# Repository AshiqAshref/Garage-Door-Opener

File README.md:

# Smart Garage Door Opener

A complete IoT garage door opener system featuring secure Bluetooth Low Energy (BLE) communication, ESP32-C3 microcontroller, custom PCB design, and Android mobile application.

## 🚀 Project Overview

This project implements a modern, secure garage door opener that can be controlled via a smartphone app. The system features:

- **Secure BLE Communication**: Encrypted pairing and authentication
- **ESP32-C3 Based Controller**: Low-power WiFi/BLE microcontroller
- **Custom PCB Design**: Professional circuit board with integrated power management
- **Android Mobile App**: Modern Material Design 3 interface
- **Visual Feedback**: 8-digit LED matrix display for status and pairing codes
- **Physical Controls**: Manual pairing button and factory reset capability

## 📁 Project Structure

```
Garage Door Opener Root/
├── Garage Door Opener Circuit/        # KiCad PCB design files
│   ├── GarageOpener.kicad_sch         # Main schematic
│   ├── GarageOpener.kicad_pcb         # PCB layout
│   ├── production files/              # Gerber files for manufacturing
│   └── parts.txt                      # Bill of materials
├── Garage Door Opener Code/
│   ├── ESP32/                         # Firmware for ESP32-C3
│   │   └── Garage Door Opener/
│   │       ├── src/main.cpp           # Main firmware code
│   │       └── platformio.ini        # PlatformIO configuration
│   └── Android/                       # Android mobile application
│       └── GarageOpenerUI/
│           └── app/src/main/          # Android app source code
├── LICENSE                            # Project license
└── README.md                          # This file
```

## 🔧 Hardware Components

### Main Components
- **ESP32-C3-MINI-1U-N4**: Main microcontroller with WiFi/BLE
- **5V Relay Module**: Controls garage door motor
- **MAX7219 LED Matrix**: 8-digit display for status and pairing codes
- **Buck Converter**: Efficient 5V power supply from mains voltage
- **3.3V Regulator**: Powers ESP32 and logic circuits

### Key Features
- **Input Voltage**: 3.8V - 32V DC input range
- **Power Consumption**: Low-power design with sleep modes
- **Protection**: ESD protection, overcurrent protection
- **Connectivity**: Micro USB for user cusom programming and debugging
- **User Interface**: Physical pairing button, LED status indicators

### PCB Specifications
- **Board Size**: Compact form factor for enclosure mounting
- **Layers**: Multi-layer design for proper power distribution
- **Components**: Surface mount components for reliability
- **Connectors**: Screw terminals for garage door connections

## 💻 Software Features

### ESP32 Firmware
- **Secure BLE Server**: Implements encrypted communication
- **Pairing Management**: Secure device pairing with passkey display
- **Display Controller**: Real-time status updates on LED matrix
- **Memory Management**: Persistent storage of paired devices
- **Factory Reset**: Complete system reset capability

### Android Application
- **Modern UI**: Material Design 3 with Jetpack Compose
- **Device Discovery**: Automatic BLE device scanning
- **Secure Pairing**: Handles BLE security and authentication
- **Device Management**: Save and manage multiple garage door openers
- **Real-time Status**: Live connection status and feedback

## 🔐 Security Features

- **Encrypted BLE Communication**: All data transmitted over encrypted channels
- **Device Authentication**: Secure pairing with passkey verification
- **Bonded Devices**: Only previously paired devices can connect
- **Timeout Protection**: Pairing mode automatically times out
- **Factory Reset**: Complete security reset capability

## 🛠️ Installation & Setup

### Hardware Assembly

1. **PCB Assembly**: Solder all components according to the schematic
2. **Power Connection**: Connect 5-32V DC power supply to input terminals
3. **Relay Wiring**: Connect relay outputs to garage door motor controls
4. **Display Connection**: Wire MAX7219 LED matrix to designated pins
5. **Enclosure**: Mount PCB in weatherproof enclosure

### Firmware Installation

1. **Install PlatformIO**: Set up PlatformIO IDE or VS Code extension
2. **Clone Repository**: Download project files
3. **Configure Platform**: Verify ESP32-C3 platform configuration
4. **Build & Upload**: Compile and flash firmware to ESP32

```bash
cd "Garage Door Opener Code/ESP32/Garage Door Opener"
pio run --target upload
```

### Android App Installation
1. **Easy Install** : Pre built app can be found in ```Garage Door Opener Code/Android/GarageOpenerUI/app/release/app-release.apk``` 

### Android App build
1. **Android Studio**: Open project in Android Studio
2. **Dependencies**: Sync Gradle dependencies
3. **Build Configuration**: Configure signing and build settings
4. **Install**: Build and install APK on Android device

```bash
cd "Garage Door Opener Code/Android/GarageOpenerUI"
./gradlew assembleRelease
```

## 📱 Usage Instructions

### Initial Setup

1. **Power On**: Connect power to the garage door opener
2. **Pairing Mode**: Press and hold the pairing button for 5 seconds
3. **Mobile App**: Open the Android app and scan for devices
4. **Select Device**: Choose "Garage" from the discovered devices list
5. **Enter Passkey**: Input the 6-digit code displayed on the LED matrix
6. **Complete Pairing**: Confirm pairing on both devices

### Daily Operation

1. **Open App**: Launch the Garage Opener app on your phone
2. **Connect**: App automatically connects to paired device
3. **Control**: Tap the garage door button to operate
4. **Status**: Monitor connection status via app interface

### Advanced Features

- **Multiple Devices**: Pair multiple garage door openers
- **Device Management**: Remove or re-pair devices as needed
- **Factory Reset**: Hold pairing button for 10 seconds to reset

## 🔌 Pin Configuration

### ESP32-C3 Pin Assignments
```cpp
#define RELAY_PIN 12        // Garage door relay control
#define BUTTON_PIN 13       // Pairing/reset button
#define DIN_PIN 21          // MAX7219 data input
#define CS_PIN 19           // MAX7219 chip select
#define CLK_PIN 18          // MAX7219 clock
```

### Power Requirements
- **Input Voltage**: 5V - 32V DC
- **ESP32 Current**: ~80mA active, ~10µA deep sleep
- **Relay Current**: ~70mA when activated
- **Display Current**: ~20mA typical

## 🐛 Troubleshooting

### Common Issues

**Cannot pair device:**
- Ensure Bluetooth is enabled on phone
- Verify device is in pairing mode (LED shows passkey)
- Check app permissions for Bluetooth access

**Relay not activating:**
- Verify power supply voltage (5V minimum)
- Check relay connections and wiring
- Test relay manually with multimeter

**Display not working:**
- Confirm MAX7219 connections and power
- Verify pin assignments in firmware
- Check display module with simple test code

**Connection drops frequently:**
- Reduce distance between phone and device
- Check for interference from other 2.4GHz devices
- Verify phone's Bluetooth Low Energy support

## 🔧 Development

### Building from Source

**Requirements:**
- PlatformIO Core 6.0+
- Android Studio Arctic Fox+
- ESP32 Arduino Core 2.0+
- Android API Level 30+

**ESP32 Development:**
```bash
# Install dependencies
pio pkg install

# Build firmware
pio run

# Upload to device
pio run --target upload

# Monitor serial output
pio device monitor
```

**Android Development:**
```bash
# Build debug APK
./gradlew assembleDebug

# Run tests
./gradlew test

# Generate release APK
./gradlew assembleRelease
```

### Code Structure

**ESP32 Firmware:**
- `main.cpp`: Main application logic and BLE server
- `LedController.hpp`: MAX7219 display management
- `platformio.ini`: Build configuration and dependencies

**Android Application:**
- `MainActivity.kt`: Main UI and app lifecycle
- `BleService.kt`: Bluetooth Low Energy communication
- `build.gradle.kts`: Build configuration and dependencies

## 📋 Bill of Materials (BOM)

### Critical Components
| Component | Part Number | Quantity | Description |
|-----------|-------------|----------|-------------|
| ESP32-C3-MINI-1U-N4 | ESP32-C3-MINI-1U-N4 | 1 | Main microcontroller |
| Relay | SRD-05VDC-SL-C | 1 | 5V SPDT relay |
| Buck Converter IC | TBD | 1 | 5V switching regulator |
| LED Matrix | MAX7219 8-digit | 1 | Status display |
| Capacitors | Various | Multiple | Power filtering |
| Resistors | Various | Multiple | Pull-ups and current limiting |

*See `parts.txt` for complete component specifications*

## 🤝 Contributing

Contributions are welcome! Please follow these guidelines:

1. **Fork the Repository**: Create your own fork
2. **Create Feature Branch**: `git checkout -b feature/new-feature`
3. **Commit Changes**: Use descriptive commit messages
4. **Push Branch**: `git push origin feature/new-feature`
5. **Create Pull Request**: Submit PR with detailed description

### Development Standards
- Follow existing code style and formatting
- Add comments for complex logic
- Test thoroughly before submitting
- Update documentation as needed

## 📄 License

This project is licensed under the MIT License - see the [LICENSE](LICENSE) file for details.

## ⚠️ Safety Warning

**ELECTRICAL SAFETY**: This device interfaces with garage door motors that operate at dangerous voltages. Installation should only be performed by qualified electricians. Always disconnect power before making connections.

**SECURITY**: While this system implements encryption, no system is 100% secure. Use appropriate physical security measures for your garage.

## 📞 Support

For questions, issues, or contributions:
- **Issues**: Use GitHub Issues for bug reports
- **Discussions**: GitHub Discussions for general questions
- **Email**: Contact project maintainer for urgent issues

## 🔄 Version History

- **v1.0**: Initial release with basic BLE functionality
- **Future**: Planned features include WiFi connectivity, web interface, and voice control integration

---

**Built with ❤️ for the maker community**

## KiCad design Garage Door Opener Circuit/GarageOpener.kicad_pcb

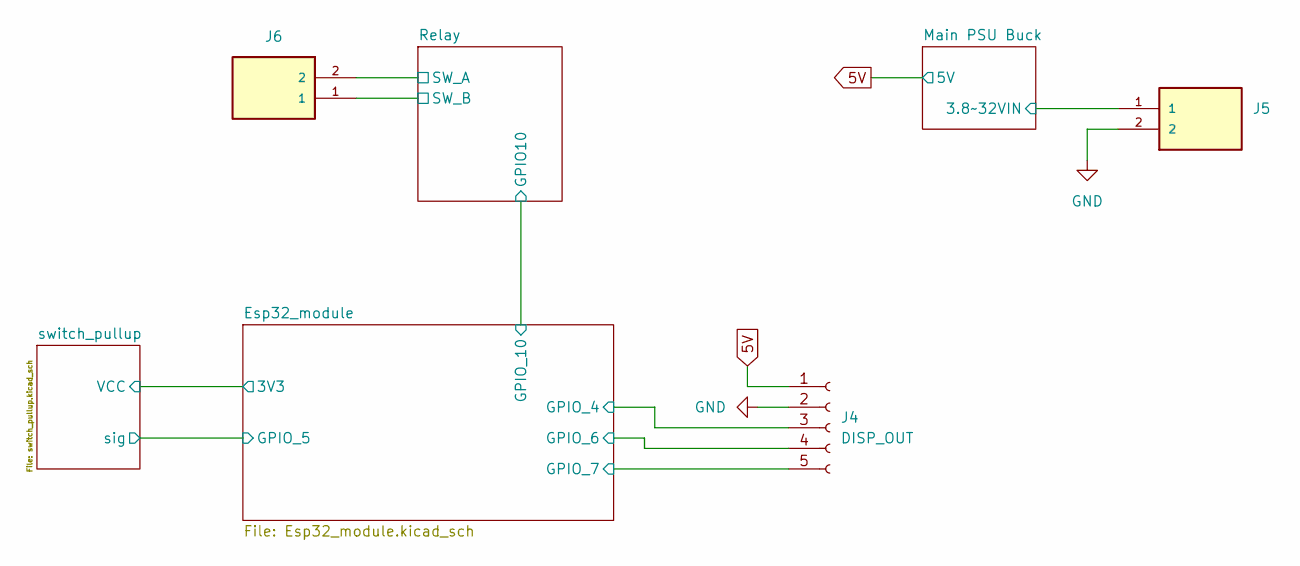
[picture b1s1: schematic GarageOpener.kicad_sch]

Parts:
J4: DISP_OUT; PinHeader_1x05_P2.54mm_Vertical
J5, J6: TB002-500-02BE; CUI_TB002-500-02BE

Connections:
5V: J4.1; also elsewhere on the board
/Esp32_module/GPIO_4: J4.3; also elsewhere on the board
/Esp32_module/GPIO_6: J4.4; also elsewhere on the board
/Esp32_module/GPIO_7: J4.5; also elsewhere on the board
/Main PSU Buck/3.8~32VIN: J5.1; also elsewhere on the board
/Relay/SW_A: J6.2; also elsewhere on the board
/Relay/SW_B: J6.1; also elsewhere on the board
GND: J4.2, J5.2; also elsewhere on the board

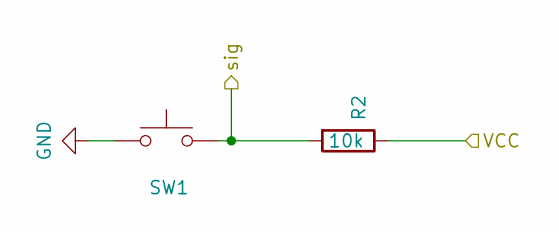
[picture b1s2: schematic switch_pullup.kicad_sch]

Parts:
R2: 10k; R_0402_1005Metric
SW1: SW_Push; SW_SPST_PTS645Sx43SMTR92

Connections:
3V3: R2.1; also elsewhere on the board
/Esp32_module/GPIO_5: R2.2, SW1.2; also elsewhere on the board
GND: SW1.1; also elsewhere on the board

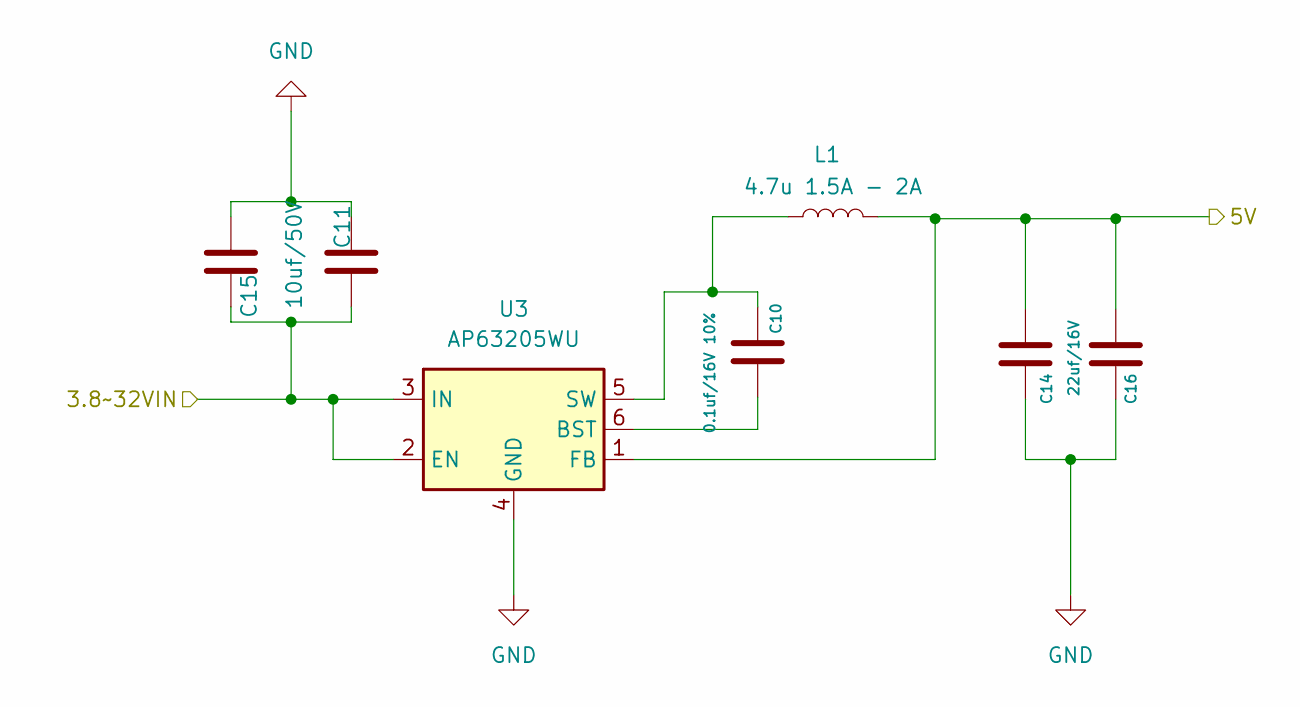
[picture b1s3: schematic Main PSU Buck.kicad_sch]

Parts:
C10: 0.1uf/16V 10%; C_0201_0603Metric
C11, C15: 10uf/50V; CAPC3225X270N
C14, C16: 22uf/16V; CAPC1608X100N
L1: 4.7u 1.5A - 2A; IND_NRS5030T100MMGJ_TAY
U3: AP63205WU; TSOT-23-6

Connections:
5V: C14.1, C16.1, L1.2, U3.1 (FB); also elsewhere on the board
/Main PSU Buck/3.8~32VIN: C11.2, C15.2, U3.2 (EN), U3.3 (IN); also elsewhere on the board
GND: C11.1, C14.2, C15.1, C16.2, U3.4 (GND); also elsewhere on the board
unnamed: C10.2, U3.6 (BST)
unnamed: C10.1, L1.1, U3.5 (SW)

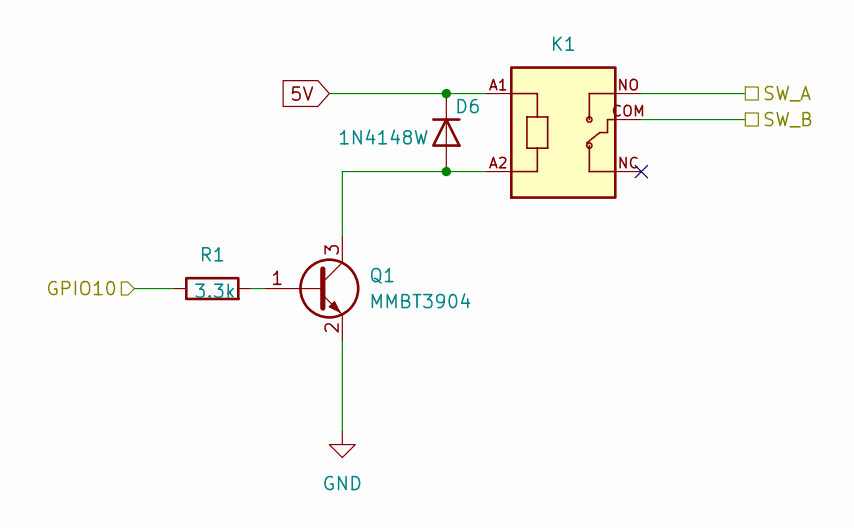
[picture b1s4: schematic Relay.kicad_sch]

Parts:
D6: 1N4148W; D_SOD-123
K1: SRD-05VDC-SL-C; RELAY_SRD-05VDC-SL-C
Q1: MMBT3904; SOT-23
R1: 3.3k; R_0603_1608Metric

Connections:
5V: D6.1 (K), K1.A1; also elsewhere on the board
/Esp32_module/GPIO_10: R1.1; also elsewhere on the board
/Relay/SW_A: K1.NO; also elsewhere on the board
/Relay/SW_B: K1.COM; also elsewhere on the board
GND: Q1.2 (E); also elsewhere on the board
unnamed: D6.2 (A), K1.A2, Q1.3 (C)
unnamed: Q1.1 (B), R1.2

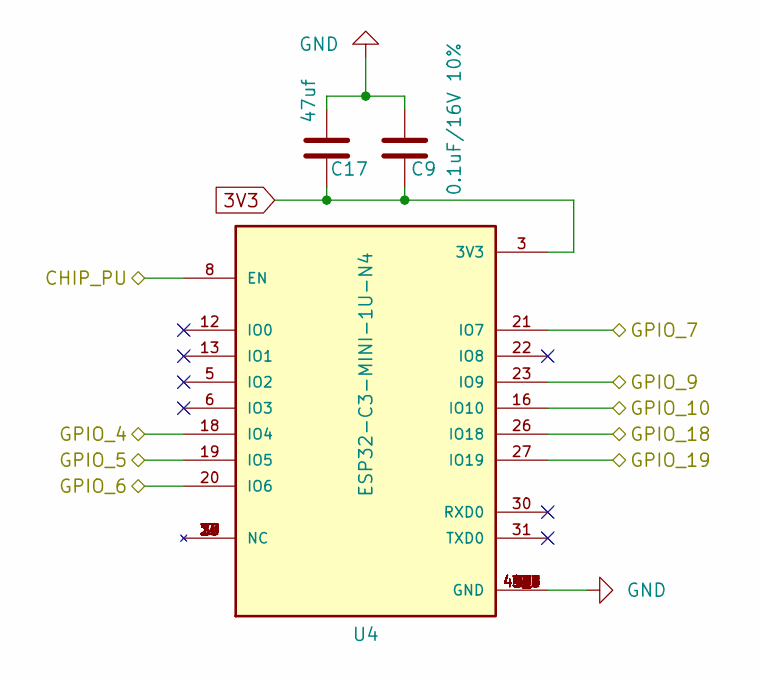
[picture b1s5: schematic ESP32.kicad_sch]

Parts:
C9: 0.1uF/16V 10%; VARC3216X85N
C17: 47uf; C_1206_3216Metric
U4: ESP32-C3-MINI-1U-N4; XCVR_ESP32-C3-MINI-1U-N4; PARTREV v1.0

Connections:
3V3: C9.1, C17.1, U4.3 (3V3); also elsewhere on the board
/Esp32_module/ESP32/CHIP_PU: U4.8 (EN); also elsewhere on the board
/Esp32_module/ESP32/GPIO_9: U4.23 (IO9); also elsewhere on the board
/Esp32_module/ESP32/GPIO_18: U4.26 (IO18); also elsewhere on the board
/Esp32_module/ESP32/GPIO_19: U4.27 (IO19); also elsewhere on the board
/Esp32_module/GPIO_4: U4.18 (IO4); also elsewhere on the board
/Esp32_module/GPIO_5: U4.19 (IO5); also elsewhere on the board
/Esp32_module/GPIO_6: U4.20 (IO6); also elsewhere on the board
/Esp32_module/GPIO_7: U4.21 (IO7); also elsewhere on the board
/Esp32_module/GPIO_10: U4.16 (IO10); also elsewhere on the board
GND: C9.2, C17.2, U4.1 (GND), U4.2 (GND), U4.11 (GND), U4.14 (GND), U4.36 (GND), U4.37 (GND), U4.38 (GND), U4.39 (GND), U4.40 (GND), U4.41 (GND), U4.42 (GND), U4.43 (GND), U4.44 (GND), U4.45 (GND), U4.46 (GND), U4.47 (GND), U4.48 (GND), U4.49_1 (GND), U4.49_2 (GND), U4.49_3 (GND), U4.49_4 (GND), U4.49_5 (GND), U4.49_6 (GND), U4.49_7 (GND), U4.49_8 (GND), U4.49_9 (GND), U4.50 (GND), U4.51 (GND), U4.52 (GND), U4.53 (GND); also elsewhere on the board

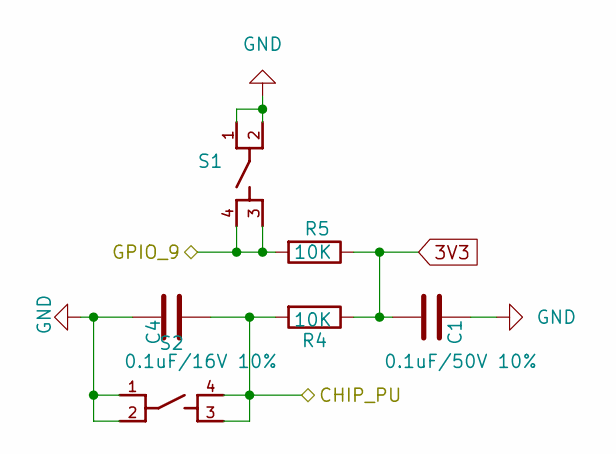
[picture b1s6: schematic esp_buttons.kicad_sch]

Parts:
C1: 0.1uF/50V 10%; C_0201_0603Metric
C4: 0.1uF/16V 10%; C_0201_0603Metric
R4, R5: 10K; R_0402_1005Metric
S1, S2: PTS526_SMG15_SMTR2_LFS; SW_PTS526_SMG15_SMTR2_LFS

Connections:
3V3: C1.1, R4.1, R5.1; also elsewhere on the board
/Esp32_module/ESP32/CHIP_PU: C4.2, R4.2, S2.3, S2.4; also elsewhere on the board
/Esp32_module/ESP32/GPIO_9: R5.2, S1.3, S1.4; also elsewhere on the board
GND: C1.2, C4.1, S1.1, S1.2, S2.1, S2.2; also elsewhere on the board

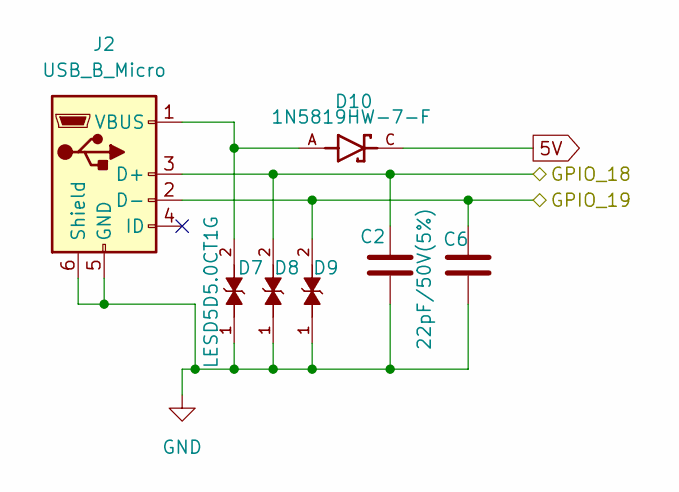
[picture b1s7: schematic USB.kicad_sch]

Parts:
C2, C6: 22pF/50V(5%); C_0201_0603Metric
D7, D8, D9: LESD5D5.0CT1G; TVS_LESD5D5.0CT1G; PARTREV O
D10: 1N5819HW-7-F; SOD3715X145N; PARTREV 18-2; DigiKey_Part_Number 1N5819HW-FDITR-ND
J2: USB_B_Micro; USB_Micro-B_Amphenol_10118194_Horizontal

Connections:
5V: D10.C; also elsewhere on the board
/Esp32_module/ESP32/GPIO_18: C2.1, D8.2, J2.3 (D+); also elsewhere on the board
/Esp32_module/ESP32/GPIO_19: C6.1, D9.2, J2.2 (D-); also elsewhere on the board
GND: C2.2, C6.2, D7.1, D8.1, D9.1, J2.5 (GND), J2.6 (Shield); also elsewhere on the board
unnamed: D7.2, D10.A, J2.1 (VBUS)

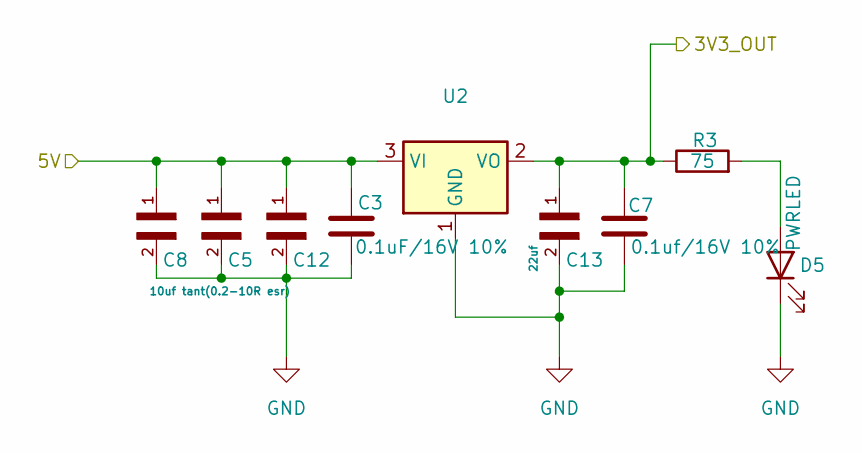
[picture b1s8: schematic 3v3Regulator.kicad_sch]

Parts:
C3: 0.1uF/16V 10%; VARC3216X85N
C5, C8, C12: 10uf tant(0.2-10R esr); C_1206_3216Metric
C7: 0.1uf/16V 10%; VARC3216X85N
C13: 22uf; C_1206_3216Metric
D5: PWRLED; 0603
R3: 75; R_0402_1005Metric
U2: AMS1117-3.3; SOT-223-3_TabPin2

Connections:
3V3: C7.1, C13.1, R3.1, U2.2 (VO); also elsewhere on the board
5V: C3.1, C5.1, C8.1, C12.1, U2.3 (VI); also elsewhere on the board
GND: C3.2, C5.2, C7.2, C8.2, C12.2, C13.2, D5.1 (K), U2.1 (GND); also elsewhere on the board
unnamed: D5.2 (A), R3.2

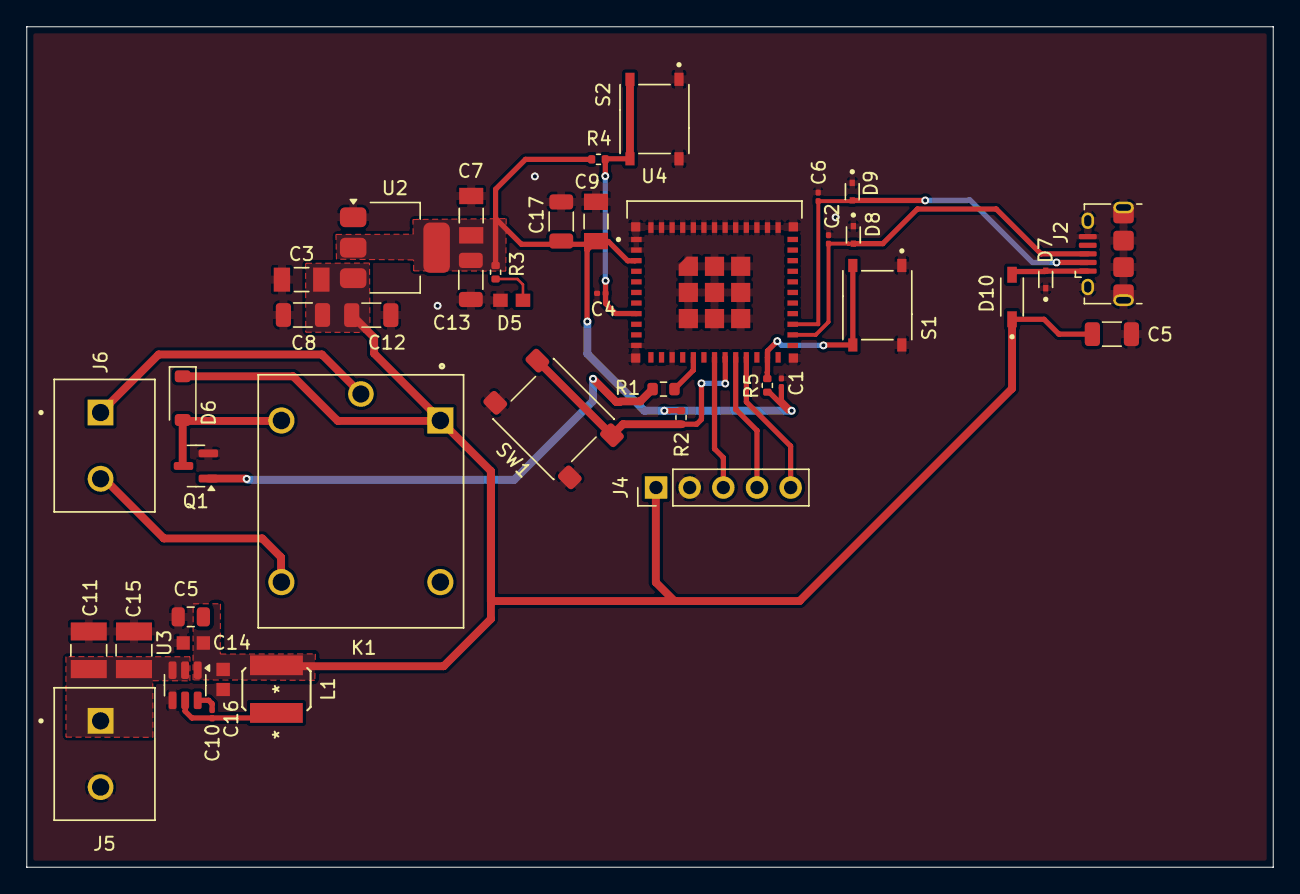
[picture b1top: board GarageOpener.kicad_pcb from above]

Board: 2 copper layers, 94.1 x 63.5 mm, 42 parts (0 on the bottom side), 21 nets.

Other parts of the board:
C5#2: 0.1uF/16V 10%; C_0805_2012Metric

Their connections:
GND: C5#2.2; also elsewhere on the board

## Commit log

2025-07-29 Create LICENSE
2025-07-29 added read me
